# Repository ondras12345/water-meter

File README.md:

# Water meter
This is a simple sensor for Sensus PN16 water meters.
It uses an infrared LED and phototransistor to sense the metal disk on the
x0.0001 m³ pointer wheel.

Sensus do sell an inductive sensor for this type of meter (Sensus HRI),
but it is a bit pricey and needs batteries to operate.

I own a small CNC mill, so I decided to mill a custom PCB that matches the
shape of the meter. This allows me to easily mount it to the meter without the
need for custom 3D printed parts.

## Hardware
KiCAD designs for the PCB are available in the [`hardware`](hardware/)
directory.

**WARNING**: Make sure to read the notes in the schematic. Since this was a
one-off project, I did not spend much time fixing potential problems I
discovered after milling the board.

## Software
This part is a bit complicated. I connected the sensor to an STM32F103 board
that handles many other sensors in the room. I don't want to share the whole
source code (it wouldn't make much sense for anyone other than me), but I will
try to include the relevant parts here:

```cpp
#define DEBOUNCE_FREQUENCY 50  // HZ
// ...

unsigned int water_meter_pulses = 0;
static volatile unsigned int pulses = 0;

#define SAMPLING_FREQUENCY DEBOUNCE_FREQUENCY  // Hz
// max flow rate should be 1,39 l / s (2*Qn)
// 2 pulses per revolution
#define DEBOUNCE_TIME 320  // ms
#define INTEGRATOR_MAX (DEBOUNCE_TIME * SAMPLING_FREQUENCY / 1000)
/**
 * Read water meter state.
 * This function should be called from a timer ISR
 * DEBOUNCE_FREQUENCY times per second.
 */
void water_meter_debounce()
{
    static unsigned int integrator = 0;

    if (digitalRead(pin_water_meter))
    {
        if (integrator < INTEGRATOR_MAX) integrator++;
    }
    else
    {
        if (integrator > 0) integrator--;
    }

    static bool output = false;
    static bool prev_output = false;
    static bool first = true;
    if (integrator == 0)
    {
        output = false;
        if (first)
        {
            first = false;
            prev_output = output;
        }
    }

    if (integrator >= INTEGRATOR_MAX)
    {
        output = true;
        if (first)
        {
            first = false;
            prev_output = output;
        }
        // this should never be needed
        integrator = INTEGRATOR_MAX;
    }

    if (output != prev_output)
    {
        prev_output = output;
        pulses++;  // incremented at every edge (0.5 l)
    }
}

void water_meter_setup()
{
    // extra pull-up might help with noise immunity
    pinMode(pin_water_meter, INPUT_PULLUP);
}

void water_meter_loop()
{
    noInterrupts();
    water_meter_pulses = pulses;
    interrupts();
}

// mqtt.cpp
void mqtt_loop()
{
    // ...
    static unsigned int prev_water_meter_pulses = 0;
    if (force_report || water_meter_pulses != prev_water_meter_pulses)
    {
        prev_water_meter_pulses = water_meter_pulses;
        char buff[3*sizeof(water_meter_pulses) + 1]; // >= number of digits + null
        snprintf(buff, sizeof buff, "%u", water_meter_pulses);
        MQTTClient.publish(MQTTtopic_water_meter_pulses, buff, true);
    }
}
```

## Home Assistant
[Home Assistant](https://www.home-assistant.io/) can be used to receive MQTT
messages sent by the device and track water consumption.

```yaml
recorder:
  exclude:
    entities:
      # do not store the intermediate sensor's state history in the database
      - sensor.water_meter_pulses

mqtt:
  sensor:
    - name: Water meter pulses
      state_topic: rolety/tele/water_meter/pulses
      availability_topic: rolety/tele/availability
      unit_of_measurement: "pulses"

template:
  - sensor:
    - name: Water meter
      unit_of_measurement: "m³"
      state: '{{ states("sensor.water_meter_pulses") | int(0) / 2000.0 }}'
      availability: '{{ has_value("sensor.water_meter_pulses") }}'
      device_class: water
      state_class: total_increasing
```
`sensor.water_meter` has the proper `state_class` and `device_class`, so it
can be used with the [energy dashboard](https://www.home-assistant.io/dashboards/energy/).

## Similar projects
- http://jheyman.github.io/blog/pages/WirelessWaterMeter/

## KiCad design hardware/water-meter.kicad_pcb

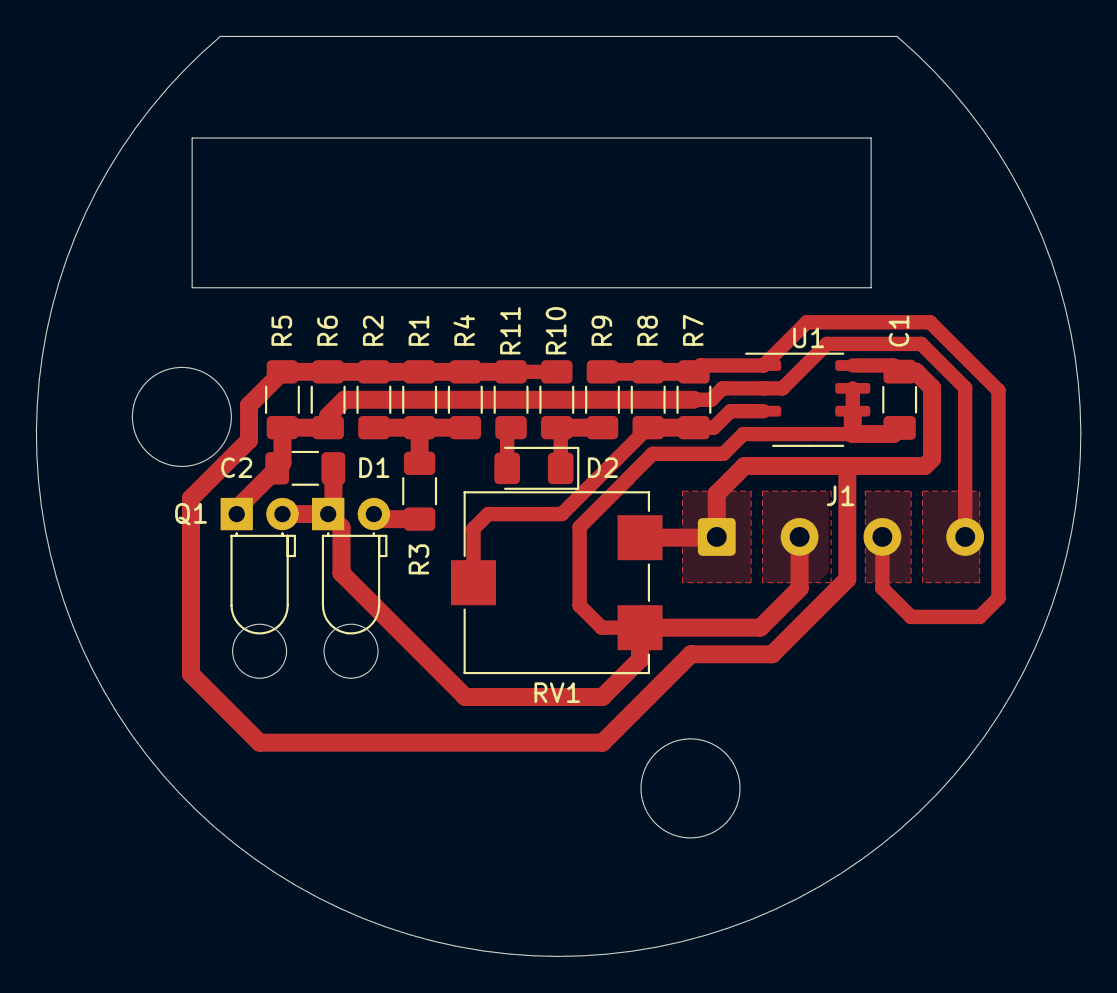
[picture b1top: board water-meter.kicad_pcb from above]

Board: 2 copper layers, 58.0 x 51.1 mm, 19 parts (0 on the bottom side), 9 nets.

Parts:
C1: 100n; C_1206_3216Metric_Pad1.33x1.80mm_HandSolder
C2: 10n; C_1206_3216Metric_Pad1.33x1.80mm_HandSolder
D1: L-934F3BT; LED_D3.0mm_Horizontal_O1.27mm_Z2.0mm
D2: LED; LED_1206_3216Metric_Pad1.42x1.75mm_HandSolder
J1: Conn_01x04; SolderWire-0.5sqmm_1x04_P4.6mm_D0.9mm_OD2.1mm
Q1: L-93DP3BT; LED_D3.0mm_Horizontal_O1.27mm_Z2.0mm
R1, R4, R7: R; R_1206_3216Metric_Pad1.30x1.75mm_HandSolder
R2, R3: 100; R_1206_3216Metric_Pad1.30x1.75mm_HandSolder
R5, R6, R10, R11: 3k3; R_1206_3216Metric_Pad1.30x1.75mm_HandSolder
R8: 22k; R_1206_3216Metric_Pad1.30x1.75mm_HandSolder
R9: 0; R_1206_3216Metric_Pad1.30x1.75mm_HandSolder
RV1: 2k2; Potentiometer_ACP_CA9-VSMD_Vertical
U1: LM393; SOIC-8_3.9x4.9mm_P1.27mm

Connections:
+3V3: C1.1, J1.1, R1.1, R2.1, R4.1, R5.1, R6.1, R10.1, R11.1, RV1.1, U1.8
GND: C1.2, C2.2, D1.1, J1.2, Q1.2, RV1.3, U1.4, U1.5, U1.6, U1.7
unnamed: C2.1, J1.4, Q1.1, R5.2, R6.2, U1.2
unnamed: D1.2, R3.2
unnamed: D2.1, R9.1, R10.2
unnamed: D2.2, R11.2
unnamed: J1.3, R7.1, R8.1, R9.2, U1.1
unnamed: R1.2, R2.2, R3.1, R4.2
unnamed: R7.2, R8.2, RV1.2, U1.3

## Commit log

2023-06-22 Add project files
2023-06-22 Fix hardware design flaws
    ... hopefully. I didn't mill a new board. Instead, I just drilled larger
    holes and sanded the edge a bit.
2023-06-23 Add README and photos
2023-06-23 Resize images in README.md
